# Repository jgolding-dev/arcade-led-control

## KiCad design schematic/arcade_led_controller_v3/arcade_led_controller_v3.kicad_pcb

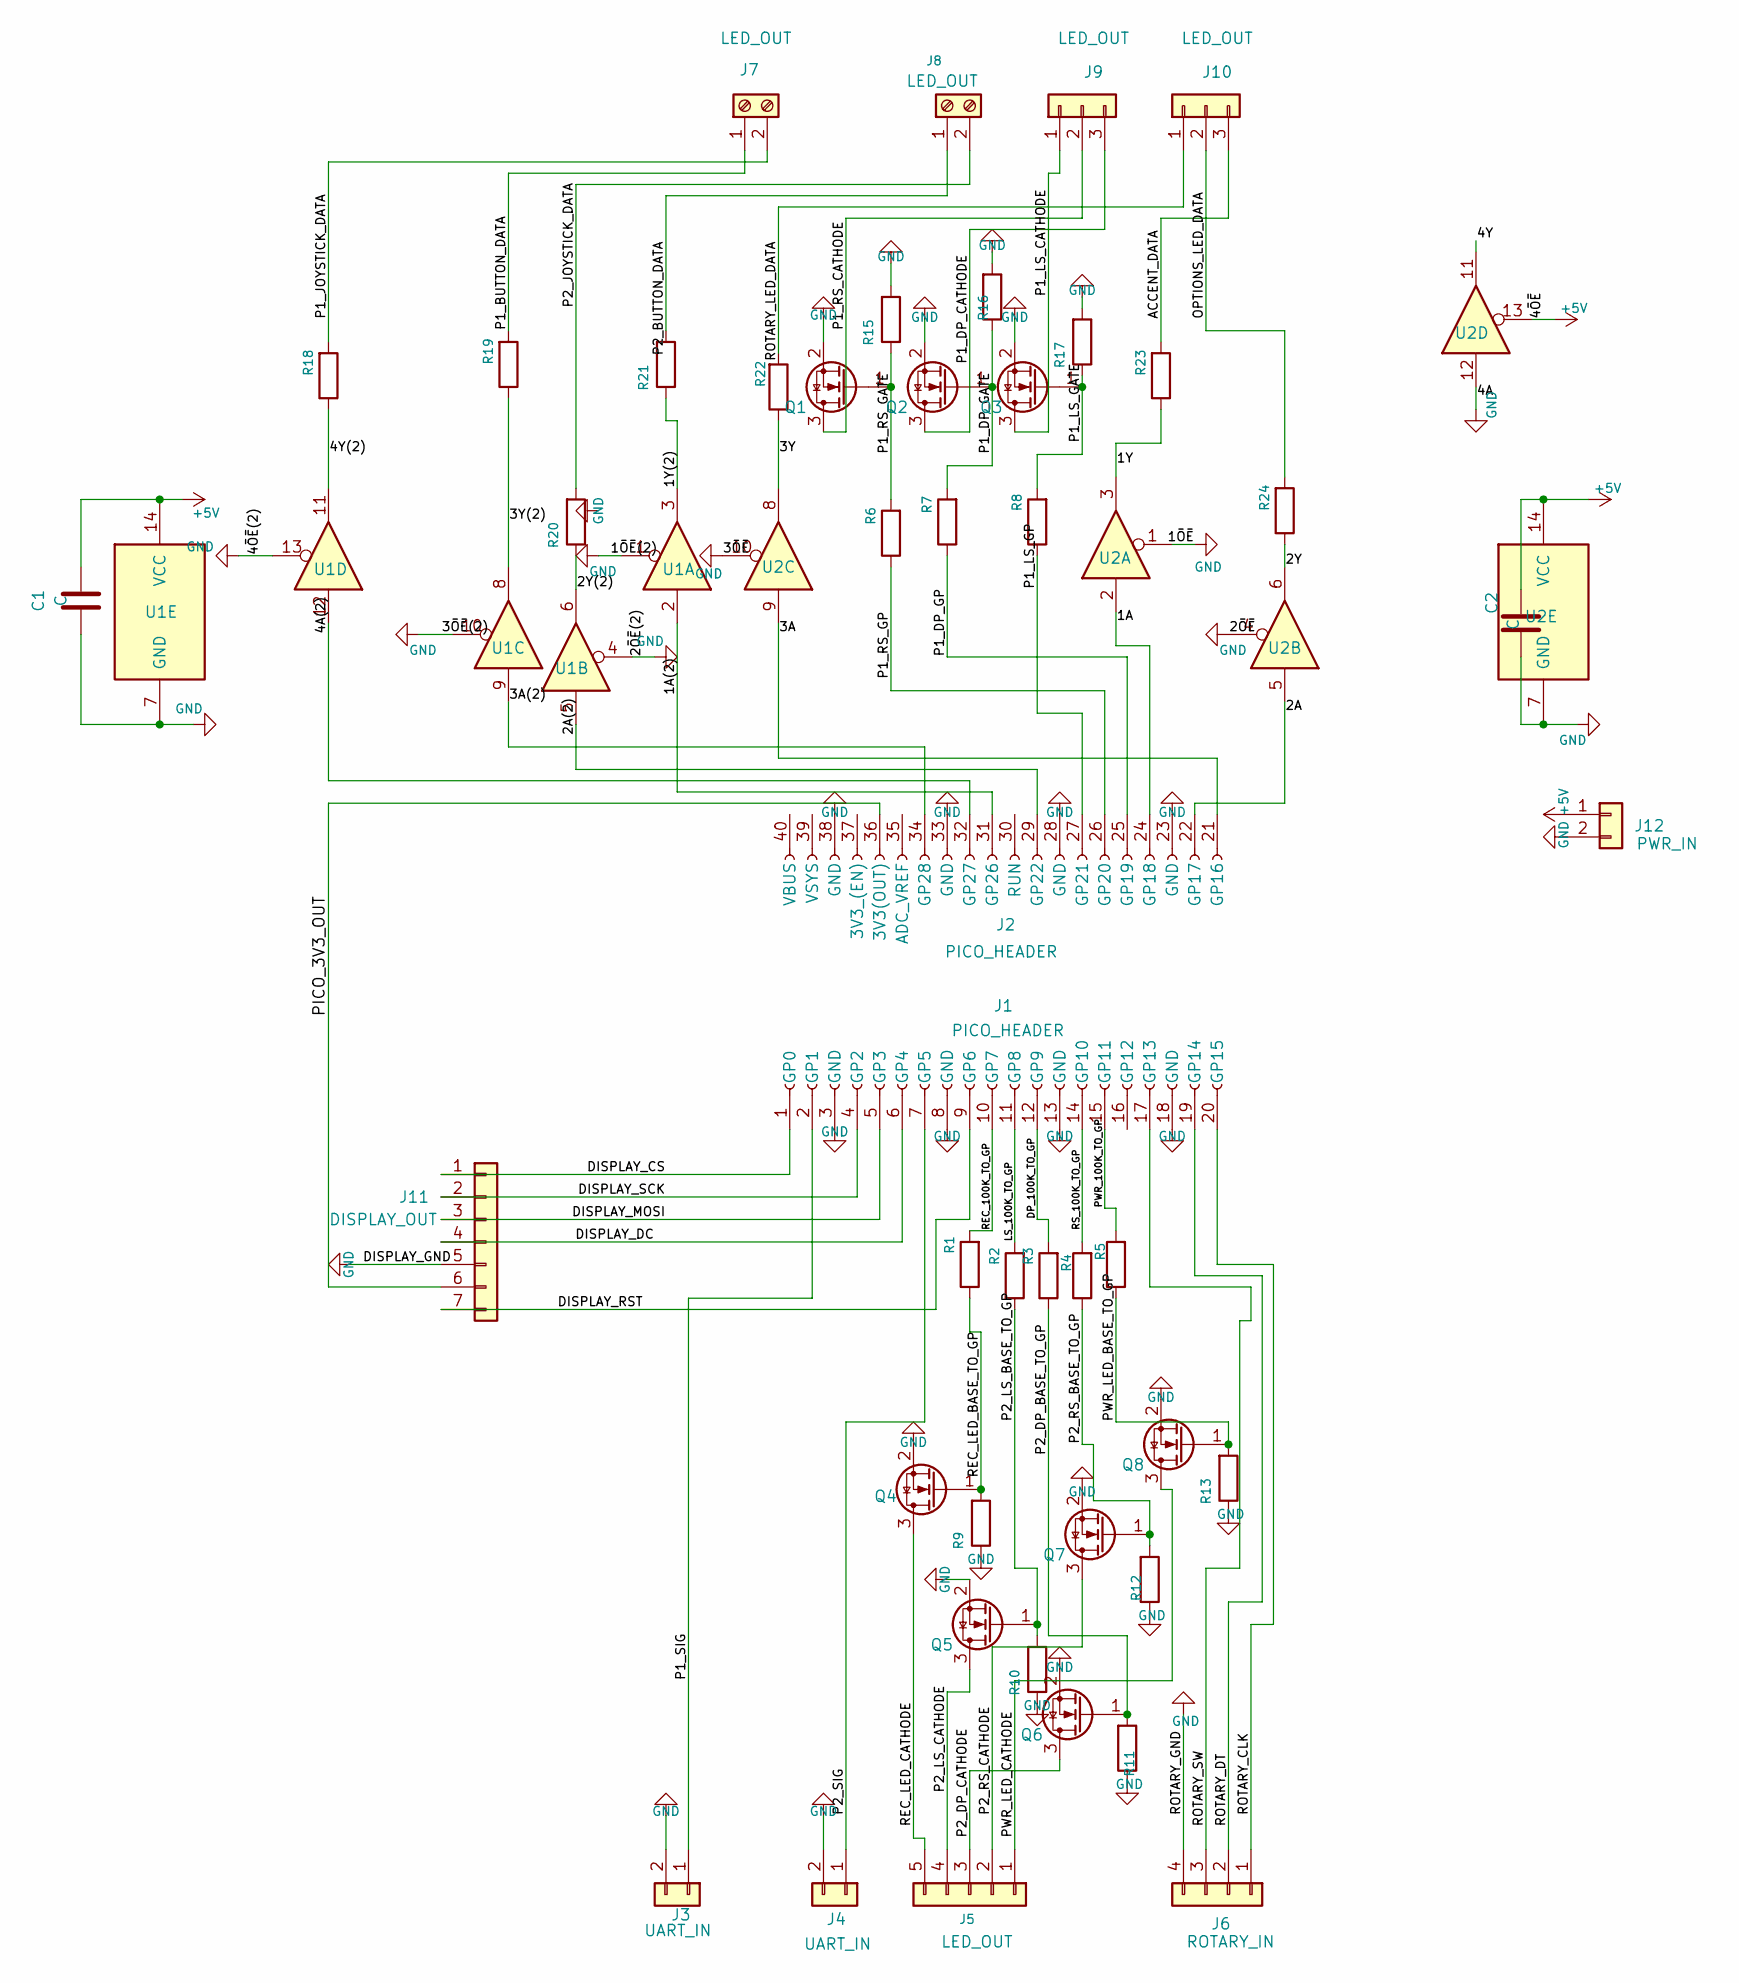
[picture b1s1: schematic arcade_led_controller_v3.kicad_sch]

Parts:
C1, C2: C; C_0805_2012Metric_Pad1.18x1.45mm_HandSolder
J1: PICO_HEADER; PinSocket_1x20_P2.54mm_Vertical_SMD_Pin1Left
J2: PICO_HEADER; PinSocket_1x20_P2.54mm_Vertical_SMD_Pin1Right
J3, J4: UART_IN; JST_PH_B2B-PH-SM4-TB_1x02-1MP_P2.00mm_Vertical
J5: LED_OUT; JST_PH_B5B-PH-SM4-TB_1x05-1MP_P2.00mm_Vertical
J6: ROTARY_IN; JST_PH_B4B-PH-SM4-TB_1x04-1MP_P2.00mm_Vertical
J7, J8: LED_OUT; JST_PH_B2B-PH-SM4-TB_1x02-1MP_P2.00mm_Vertical
J9, J10: LED_OUT; JST_PH_B3B-PH-SM4-TB_1x03-1MP_P2.00mm_Vertical
J11: DISPLAY_OUT; JST_PH_B7B-PH-SM4-TB_1x07-1MP_P2.00mm_Vertical
J12: PWR_IN; TerminalBlock_MetzConnect_Type086_RT03402HBLC_1x02_P3.81mm_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
Q1, Q2, Q3, Q4, Q5, Q6, Q7, Q8: Q_NMOS_GDS; SOT-23
R1, R2, R3, R4, R5, R6, R7, R8: 220Ω; R_0805_2012Metric_Pad1.20x1.40mm_HandSolder
R9, R10, R11, R12, R13, R15, R16, R17: 100kΩ; R_0805_2012Metric_Pad1.20x1.40mm_HandSolder
R18, R19, R20, R21, R22, R23, R24: 330Ω; R_0805_2012Metric_Pad1.20x1.40mm_HandSolder
U1, U2: 74AHCT125; SOIC-14_3.9x8.7mm_P1.27mm

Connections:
+5V: C1.2, C2.2, J12.1, U1.14 (VCC), U2.13, U2.14 (VCC); also elsewhere on the board
/1A: J2.24 (GP18), U2.2
/1A(2): J2.31 (GP26), U1.2
/1Y: R23.1, U2.3
/1Y(2): R21.1, U1.3
/2A: J2.22 (GP17), U2.5
/2A(2): J2.29 (GP22), U1.5
/2Y: R24.1, U2.6
/2Y(2): R20.1, U1.6
/3A: J2.21 (GP16), U2.9
/3A(2): J2.34 (GP28), U1.9
/3Y: R22.1, U2.8
/3Y(2): R19.1, U1.8
/4A(2): J2.32 (GP27), U1.12
/4Y: U2.11
/4Y(2): R18.1, U1.11
/ACCENT_DATA: J10.3, R23.2
/DISPLAY_CS: J1.1 (GP0), J11.1
/DISPLAY_DC: J1.6 (GP4), J11.4
/DISPLAY_MOSI: J1.5 (GP3), J11.3
/DISPLAY_RST: J1.9 (GP6), J11.7
/DISPLAY_SCK: J1.4 (GP2), J11.2
/DP_100K_TO_GP: J1.12 (GP9), R3.2
/LS_100K_TO_GP: J1.11 (GP8), R2.2
/OPTIONS_LED_DATA: J10.2, R24.2
/P1_BUTTON_DATA: J7.1, R19.2
/P1_DP_CATHODE: J9.3, Q2.3 (D)
/P1_DP_GATE: Q2.1 (G), R7.2, R16.1
/P1_DP_GP: J2.25 (GP19), R7.1
/P1_JOYSTICK_DATA: J7.2, R18.2
/P1_LS_CATHODE: J9.1, Q3.3 (D)
/P1_LS_GATE: Q3.1 (G), R8.2, R17.1
/P1_LS_GP: J2.27 (GP21), R8.1
/P1_RS_CATHODE: J9.2, Q1.3 (D)
/P1_RS_GATE: Q1.1 (G), R6.2, R15.1
/P1_RS_GP: J2.26 (GP20), R6.1
/P1_SIG: J1.2 (GP1), J3.1
/P2_BUTTON_DATA: J8.1, R21.2
/P2_DP_BASE_TO_GP: Q6.1 (G), R3.1, R11.2
/P2_DP_CATHODE: J5.3, Q6.3 (D)
/P2_JOYSTICK_DATA: J8.2, R20.2
/P2_LS_BASE_TO_GP: Q5.1 (G), R2.1, R10.2
/P2_LS_CATHODE: J5.4, Q5.3 (D)
/P2_RS_BASE_TO_GP: Q7.1 (G), R4.1, R12.2
/P2_RS_CATHODE: J5.2, Q7.3 (D)
/P2_SIG: J1.7 (GP5), J4.1
/PICO_3V3_OUT: J2.36 (3V3(OUT)), J11.6
/PWR_100K_TO_GP: J1.15 (GP11), R5.2
/PWR_LED_BASE_TO_GP: Q8.1 (G), R5.1, R13.2
/PWR_LED_CATHODE: J5.1, Q8.3 (D)
/REC_100K_TO_GP: J1.10 (GP7), R1.2
/REC_LED_BASE_TO_GP: Q4.1 (G), R1.1, R9.2
/REC_LED_CATHODE: J5.5, Q4.3 (D)
/ROTARY_CLK: J1.20 (GP15), J6.1
/ROTARY_DT: J1.19 (GP14), J6.2
/ROTARY_LED_DATA: J10.1, R22.2
/ROTARY_SW: J1.17 (GP13), J6.3
/RS_100K_TO_GP: J1.14 (GP10), R4.2
GND: C1.1, C2.1, J1.3 (GND), J1.8 (GND), J1.13 (GND), J1.18 (GND), J2.23 (GND), J2.28 (GND), J2.33 (GND), J2.38 (GND), J3.2, J4.2, J6.4, J11.5, J12.2, Q1.2 (S), Q2.2 (S), Q3.2 (S), Q4.2 (S), Q5.2 (S), Q6.2 (S), Q7.2 (S), Q8.2 (S), R9.1, R10.1, R11.1, R12.1, R13.1, R15.2, R16.2, R17.2, U1.1, U1.4, U1.7 (GND), U1.10, U1.13, U2.1, U2.4, U2.7 (GND), U2.10, U2.12; also elsewhere on the board

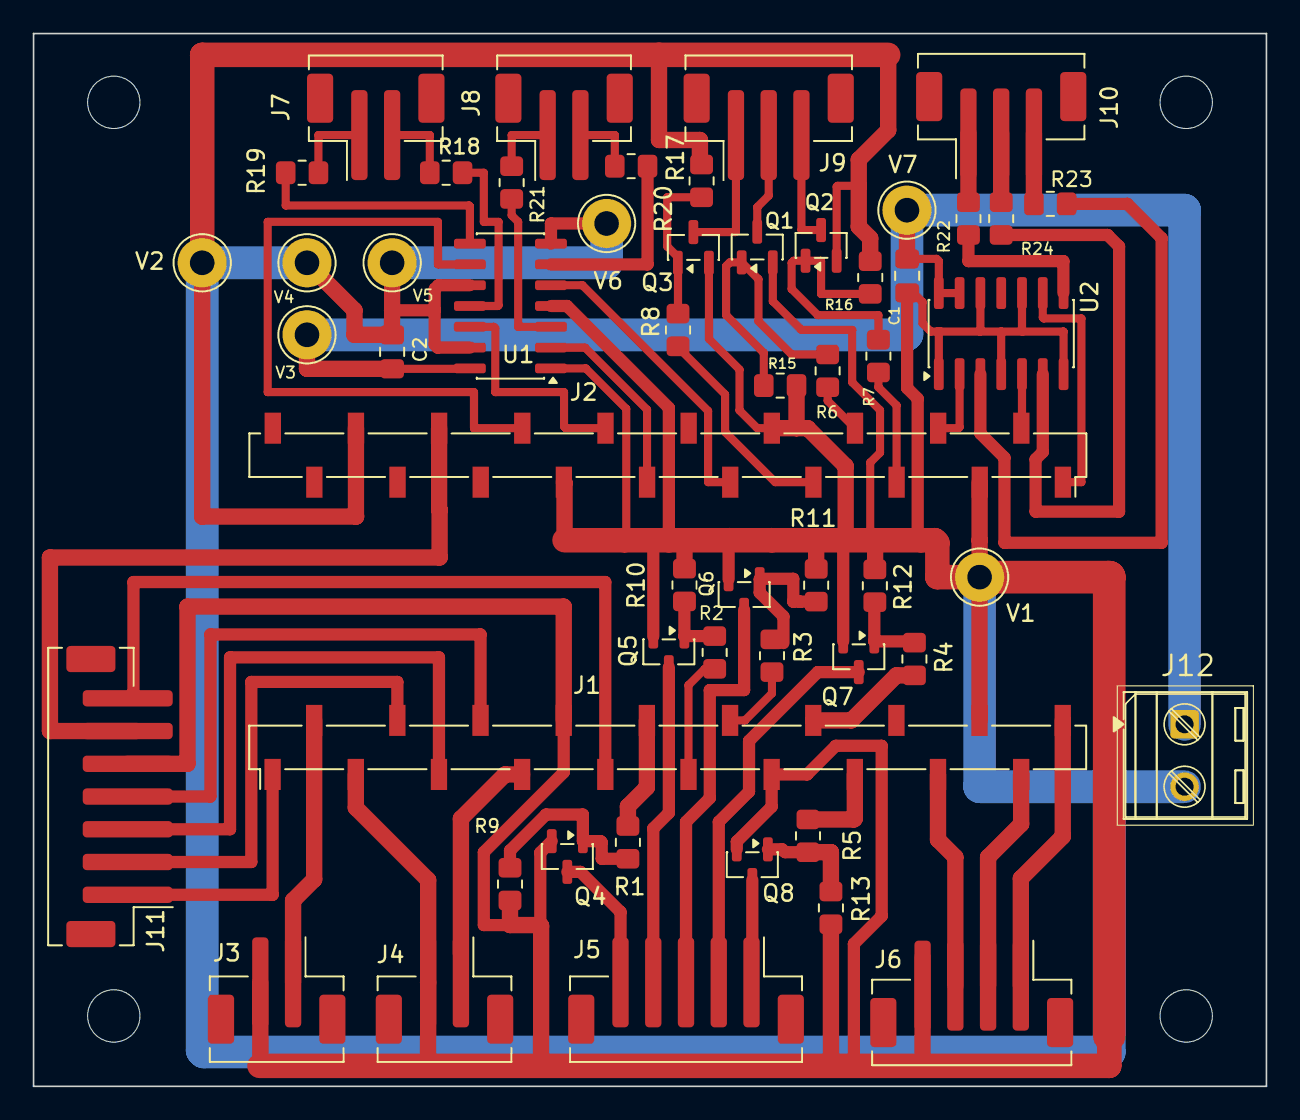
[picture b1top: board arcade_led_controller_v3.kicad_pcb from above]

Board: 2 copper layers, 75.3 x 64.3 mm, 54 parts (0 on the bottom side), 58 nets.

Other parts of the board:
V1, V2, V3, V4, V5, V6, V7: TestPoint_THTPad_D3.0mm_Drill1.5mm

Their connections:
+5V: V3.1, V7.1; also elsewhere on the board
GND: V1.1, V2.1, V4.1, V5.1, V6.1; also elsewhere on the board

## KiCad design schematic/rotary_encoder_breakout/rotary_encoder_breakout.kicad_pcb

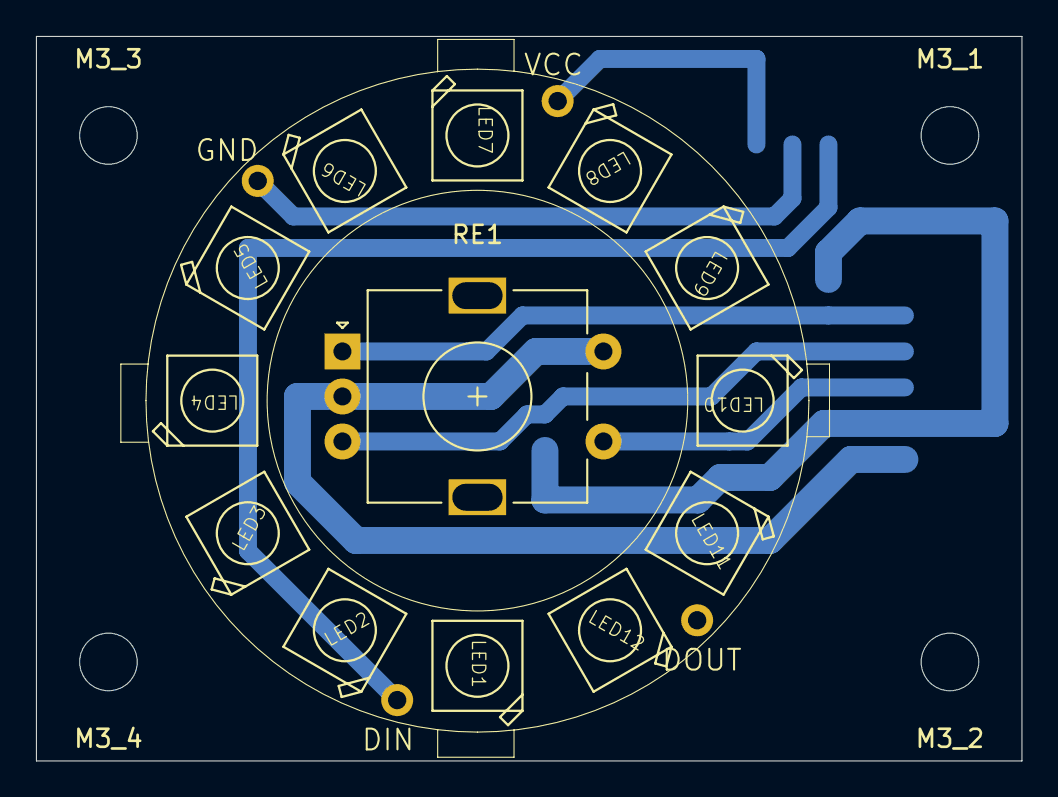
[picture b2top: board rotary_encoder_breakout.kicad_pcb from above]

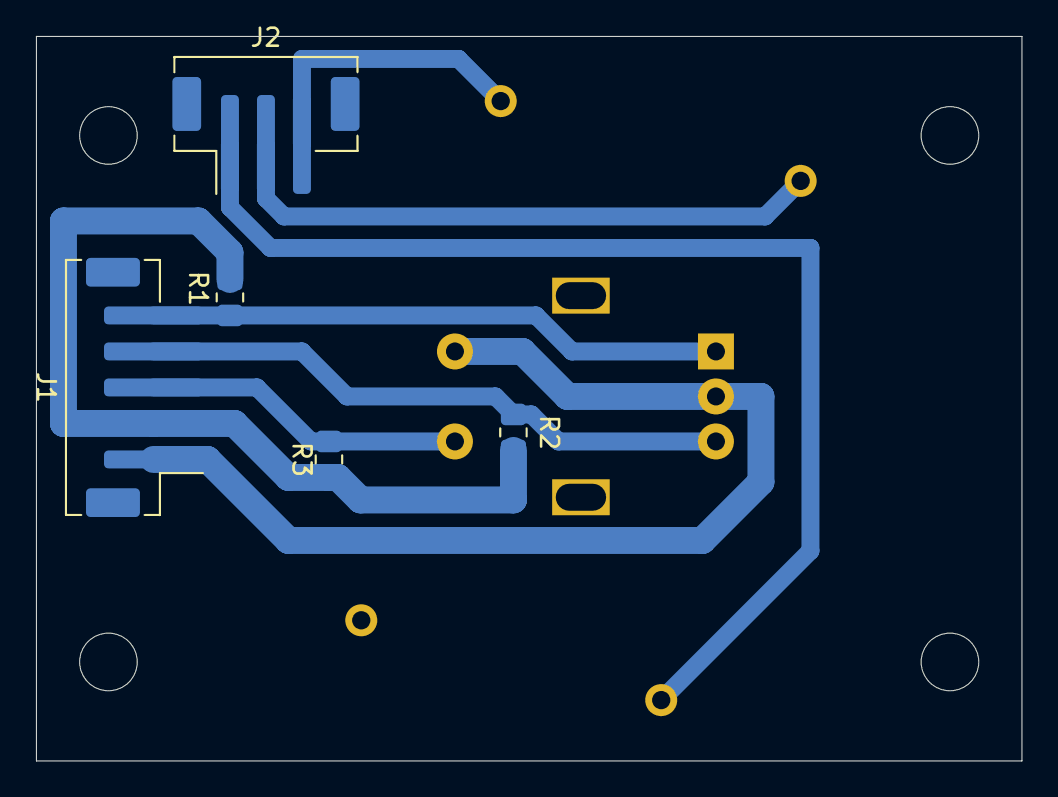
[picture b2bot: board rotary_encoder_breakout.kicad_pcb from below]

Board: 2 copper layers, 54.8 x 40.2 mm, 41 parts (10 on the bottom side), 7 nets.

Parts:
C2, C4, C6, C9, C10: 1uF; C0603_334
DIN: 1X01-CLEANBIG
DOUT: 1X01-CLEANBIG
GND: 1X01-CLEANBIG
J1: JST_Header_01x05; JST_PH_B5B-PH-SM4-TB_1x05-1MP_P2.00mm_Vertical
J2: Conn_01x04; JST_PH_B3B-PH-SM4-TB_1x03-1MP_P2.00mm_Vertical
LED1, LED2, LED3, LED4, LED5, LED6, LED7, LED8, LED9, LED10, LED11, LED12: WS2812B_5050N; WS2812B-NARROW
M3_1, M3_2, M3_3, M3_4: MountingHole_3.2mm_M3
PLABEL0: PLABEL0
PLABEL1: PLABEL1
PLABEL2: PLABEL2
PLABEL3: PLABEL3
PLABEL4: PLABEL4
PLABEL5: PLABEL5
PLABEL6: PLABEL6
PLABEL7: PLABEL7
PLABEL8: PLABEL8
R1: 470; 0603-NO
R1#2, R2, R3: 10k; R_0805_2012Metric_Pad1.20x1.40mm_HandSolder
RE1: RotaryEncoder_Switch; RotaryEncoder_Alps_EC11E-Switch_Vertical_H20mm
VCC: 1X01-CLEANBIG

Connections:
/CLK: J1.5, R1#2.2, RE1.A
/DT: J1.4, R2.1, RE1.B
/LED_DATA_IN: DIN.1, J2.1
/SW: J1.3, R3.2, RE1.S1
GND: GND.1, J1.1, J2.2, RE1.C, RE1.S2
VCC: J1.2, R1#2.1, R2.2, R3.1
VDD: J2.3, VCC.1

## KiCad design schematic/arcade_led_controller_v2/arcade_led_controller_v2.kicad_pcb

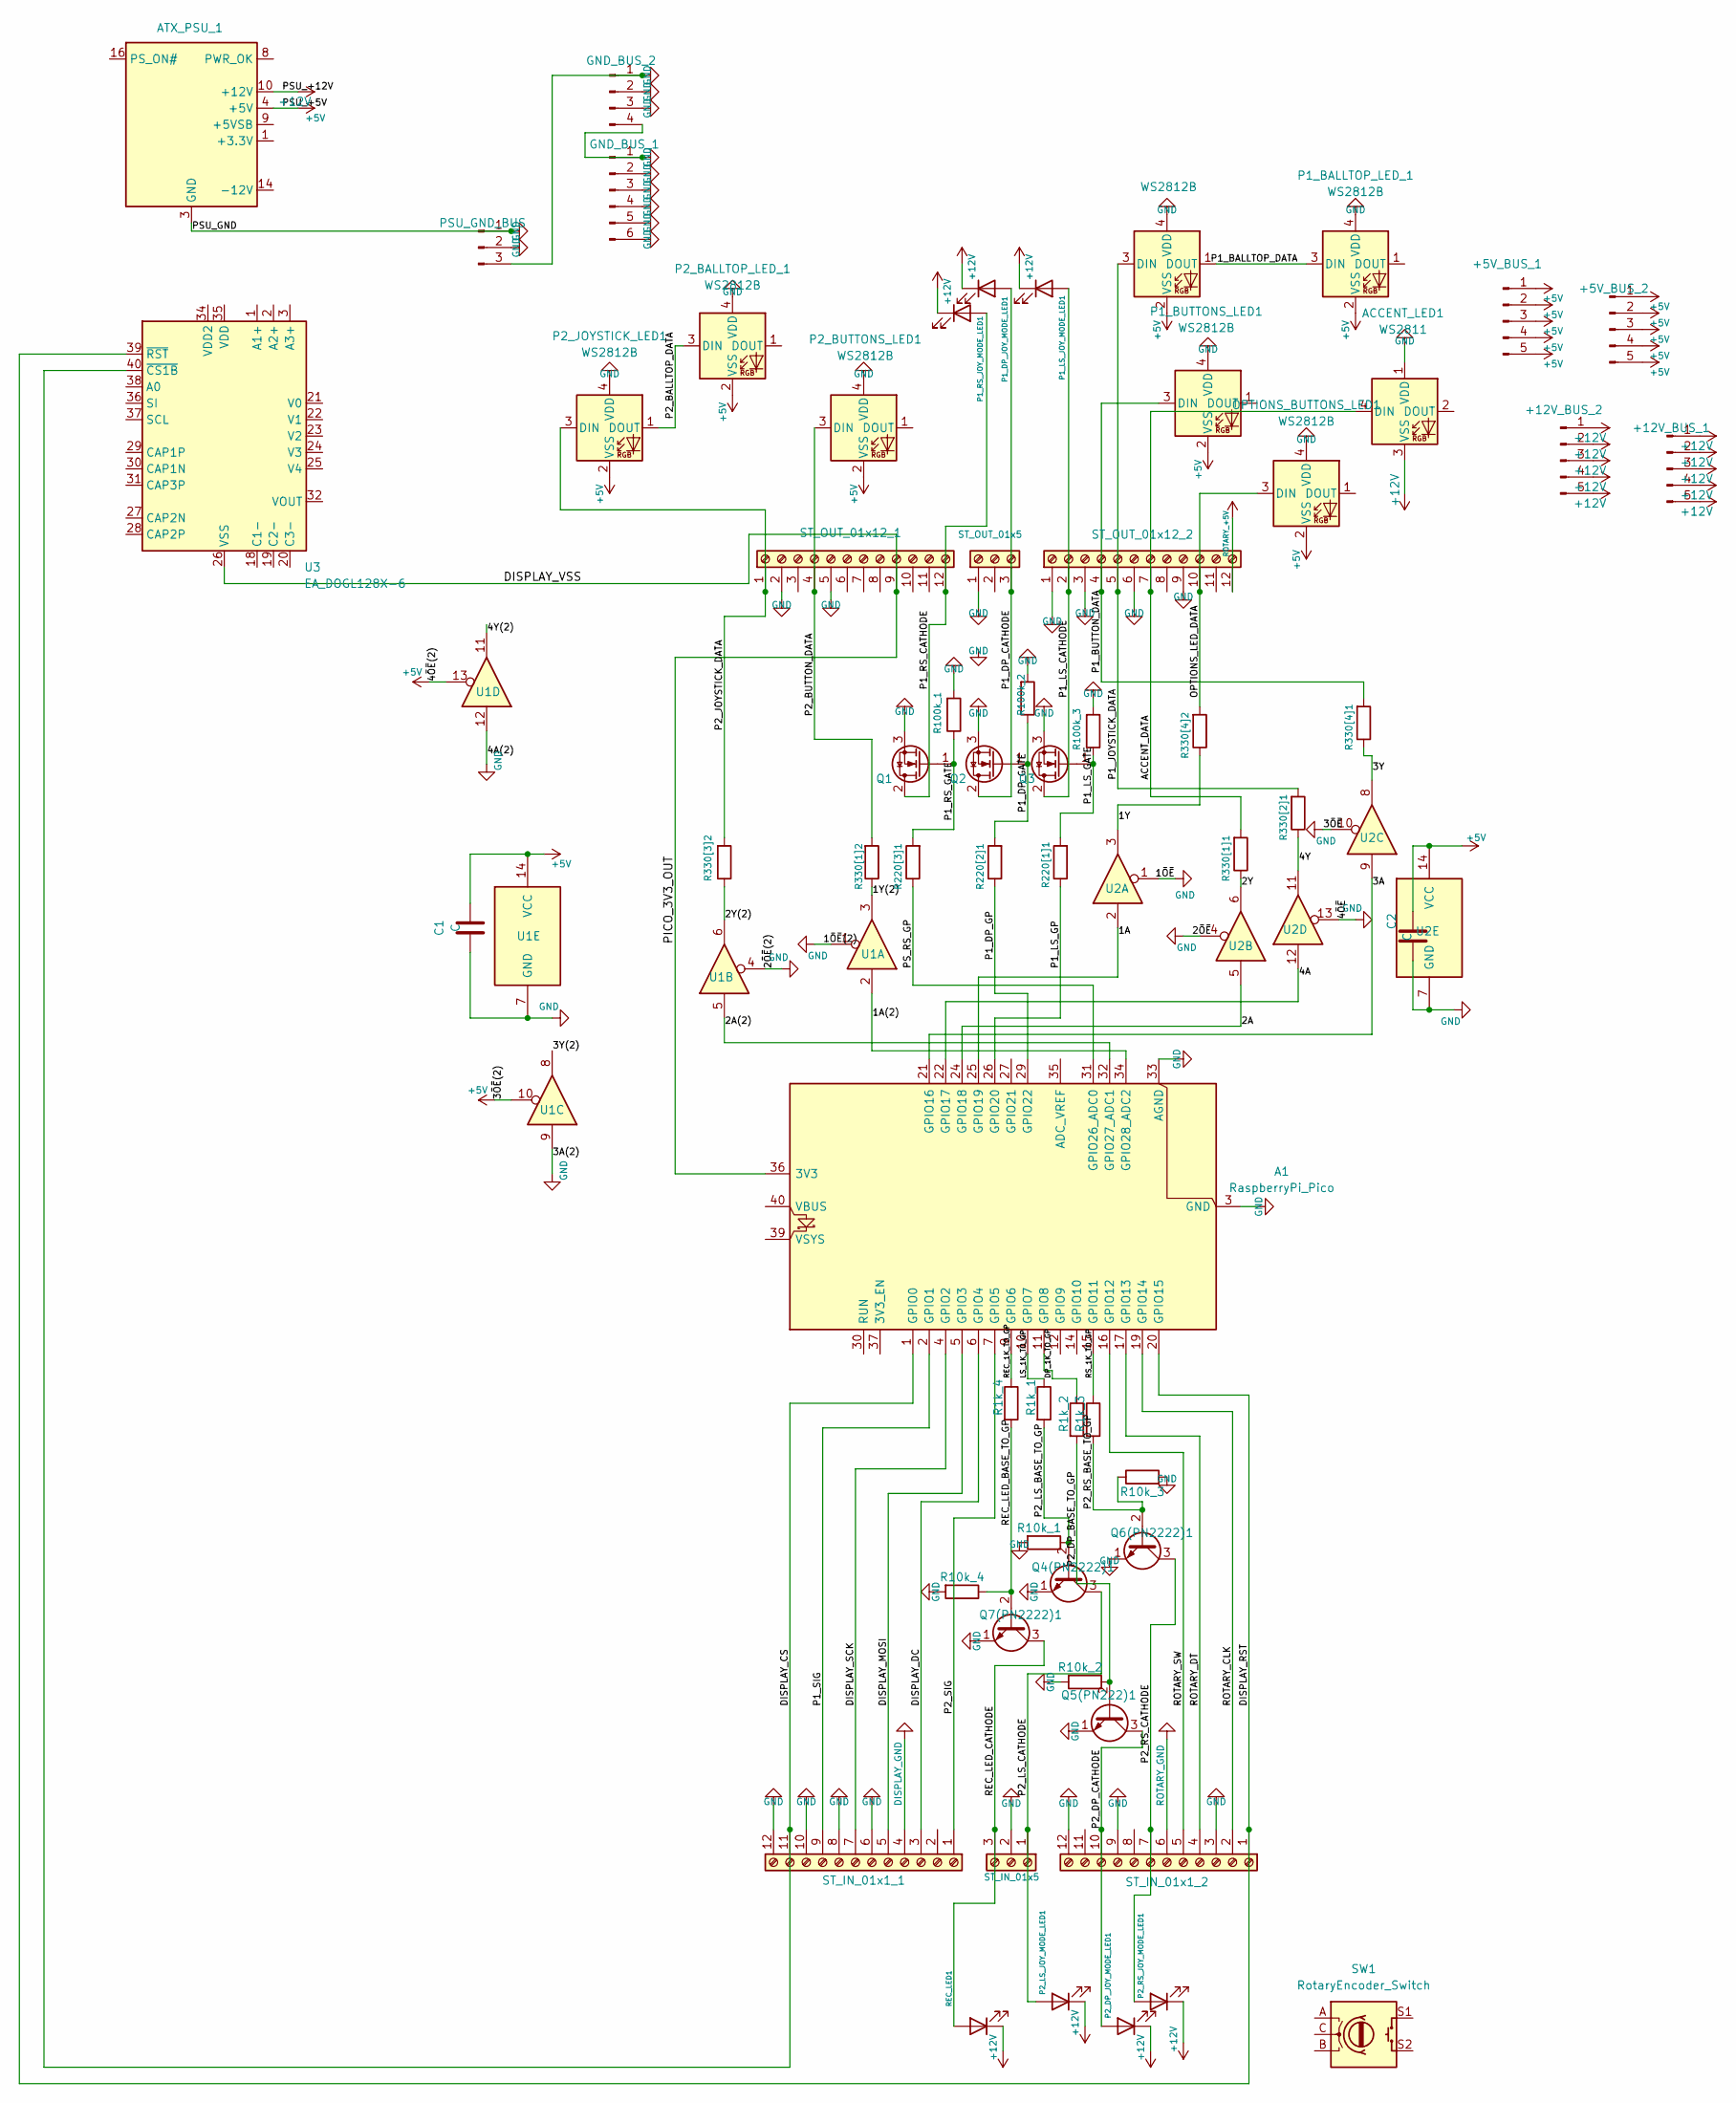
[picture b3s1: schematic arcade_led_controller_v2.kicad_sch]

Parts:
+5V_BUS_1, +5V_BUS_2: Conn_01x05_Pin; Wago_734-165_1x05_P3.50mm_Horizontal
+12V_BUS_1, +12V_BUS_2: Conn_01x05_Pin; TerminalBlock_WAGO_233-505_2x05_P2.54mm
A1: RaspberryPi_Pico; RaspberryPi_Pico_Common_THT
ACCENT_LED1: WS2811; LED_WS2812B_PLCC4_5.0x5.0mm_P3.2mm
ATX_PSU_1: ATX-24; Molex_Mini-Fit_Jr_5566-24A_2x12_P4.20mm_Vertical
C1, C2: C; C_Disc_D3.0mm_W1.6mm_P2.50mm
J1: GND_BUS_1; TerminalBlock_WAGO_233-506_2x06_P2.54mm
J2: GND_BUS_2; TerminalBlock_WAGO_233-504_2x04_P2.54mm
J3: PSU_GND_BUS; Wago_734-163_1x03_P3.50mm_Horizontal
OPTIONS_BUTTONS_LED1: WS2812B; LED_WS2812B-2020_PLCC4_2.0x2.0mm
P1_BALLTOP_LED_1, P1_BUTTONS_LED1, P1_JOYSTICK_LED1, P2_BALLTOP_LED_1, P2_BUTTONS_LED1, P2_JOYSTICK_LED1: WS2812B; LED_WS2812B-2020_PLCC4_2.0x2.0mm
P1_DP_JOY_MODE_LED1, P1_LS_JOY_MODE_LED1, P1_RS_JOY_MODE_LED1, P2_DP_JOY_MODE_LED1, P2_LS_JOY_MODE_LED1, P2_RS_JOY_MODE_LED1: LED; LED_D1.8mm_W1.8mm_H2.4mm_Horizontal_O3.81mm_Z1.6mm
Q1, Q2, Q3: Q_NMOS_GDS; TO-220-3_Vertical
Q4(PN2222)1, Q5(PN222)1, Q6(PN2222)1, Q7(PN2222)1: PN2222A; TO-92_Inline_Wide
R1k_1, R1k_2, R1k_3, R1k_4: 1kΩ; R_Axial_DIN0204_L3.6mm_D1.6mm_P5.08mm_Horizontal
R10k_1, R10k_2, R10k_3, R10k_4: 10kΩ; R_Axial_DIN0204_L3.6mm_D1.6mm_P5.08mm_Horizontal
R100k_1, R100k_2, R100k_3: 100kΩ; R_Axial_DIN0204_L3.6mm_D1.6mm_P5.08mm_Horizontal
R220[1]1, R220[2]1, R220[3]1: 220Ω; R_Axial_DIN0204_L3.6mm_D1.6mm_P5.08mm_Horizontal
R330[1]1, R330[1]2, R330[2]1, R330[3]2, R330[4]1, R330[4]2: 330Ω; R_Axial_DIN0204_L3.6mm_D1.6mm_P5.08mm_Horizontal
REC_LED1: LED; LED_D1.8mm_W1.8mm_H2.4mm_Horizontal_O3.81mm_Z1.6mm
ST_IN_01x1_1, ST_IN_01x1_2: Screw_Terminal_01x12; TerminalBlock_Phoenix_MPT-0,5-12-2.54_1x12_P2.54mm_Horizont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
ST_IN_01x5: Screw_Terminal_01x05; TerminalBlock_Phoenix_MPT-0,5-3-2.54_1x03_P2.54mm_Horizontal
ST_OUT_01x5: Screw_Terminal_01x05; TerminalBlock_Phoenix_MPT-0,5-3-2.54_1x03_P2.54mm_Horizontal
ST_OUT_01x12_1, ST_OUT_01x12_2: Screw_Terminal_01x12; TerminalBlock_Phoenix_MPT-0,5-12-2.54_1x12_P2.54mm_Horizont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
SW1: RotaryEncoder_Switch
U1, U2: 74AHCT125; DIP-14_W7.62mm
U3: EA_DOGL128X-6; EA_DOGL128-6

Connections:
+5V: +5V_BUS_1.1, +5V_BUS_1.2, +5V_BUS_1.3, +5V_BUS_1.4, +5V_BUS_1.5, +5V_BUS_2.1, +5V_BUS_2.2, +5V_BUS_2.3, +5V_BUS_2.4, +5V_BUS_2.5, ATX_PSU_1.4 (+5V), ATX_PSU_1.6 (+5V), ATX_PSU_1.21 (+5V), ATX_PSU_1.22 (+5V), ATX_PSU_1.23 (+5V), C1.2, C2.2, OPTIONS_BUTTONS_LED1.2 (VSS), P1_BALLTOP_LED_1.2 (VSS), P1_BUTTONS_LED1.2 (VSS), P1_JOYSTICK_LED1.2 (VSS), P2_BALLTOP_LED_1.2 (VSS), P2_BUTTONS_LED1.2 (VSS), P2_JOYSTICK_LED1.2 (VSS), U1.10, U1.13, U1.14 (VCC), U2.14 (VCC)
+12V: +12V_BUS_1.1, +12V_BUS_1.2, +12V_BUS_1.3, +12V_BUS_1.4, +12V_BUS_1.5, +12V_BUS_2.1, +12V_BUS_2.2, +12V_BUS_2.3, +12V_BUS_2.4, +12V_BUS_2.5, ACCENT_LED1.3 (VSS), ATX_PSU_1.10 (+12V), ATX_PSU_1.11 (+12V), P1_DP_JOY_MODE_LED1.1 (K), P1_LS_JOY_MODE_LED1.1 (K), P1_RS_JOY_MODE_LED1.1 (K), P2_DP_JOY_MODE_LED1.1 (K), P2_LS_JOY_MODE_LED1.1 (K), P2_RS_JOY_MODE_LED1.1 (K), REC_LED1.1 (K)
/1A: A1.25 (GPIO19), U2.2
/1A(2): A1.34 (GPIO28_ADC2), U1.2
/1Y: R330[4]2.1, U2.3
/1Y(2): R330[1]2.1, U1.3
/2A: A1.24 (GPIO18), U2.5
/2A(2): A1.32 (GPIO27_ADC1), U1.5
/2Y: R330[1]1.1, U2.6
/2Y(2): R330[3]2.1, U1.6
/3A: A1.21 (GPIO16), U2.9
/3Y: R330[4]1.1, U2.8
/3Y(2): U1.8
/4A: A1.22 (GPIO17), U2.12
/4Y: R330[2]1.1, U2.11
/4Y(2): U1.11
/ACCENT_DATA: ACCENT_LED1.4 (DIN), R330[1]1.2, ST_OUT_01x12_2.7
/DISPLAY_CS: A1.1 (GPIO0), ST_IN_01x1_1.11, U3.40 (~CS1B)
/DISPLAY_DC: A1.6 (GPIO4), ST_IN_01x1_1.3
/DISPLAY_MOSI: A1.5 (GPIO3), ST_IN_01x1_1.5
/DISPLAY_RST: A1.20 (GPIO15), ST_IN_01x1_2.1, U3.39 (~RST)
/DISPLAY_SCK: A1.4 (GPIO2), ST_IN_01x1_1.7
/DISPLAY_VSS: A1.36 (3V3), ST_OUT_01x12_1.9, U3.26 (VSS), U3.33 (VSS)
/DP_1K_TO_GP: A1.11 (GPIO8), R1k_2.1
/LS_1K_TO_GP: A1.10 (GPIO7), R1k_1.1
/OPTIONS_LED_DATA: OPTIONS_BUTTONS_LED1.3 (DIN), R330[4]2.2, ST_OUT_01x12_2.10
/P1_BALLTOP_DATA: P1_BALLTOP_LED_1.3 (DIN), P1_JOYSTICK_LED1.1 (DOUT)
/P1_BUTTON_DATA: P1_BUTTONS_LED1.3 (DIN), R330[4]1.2, ST_OUT_01x12_2.4
/P1_DP_CATHODE: P1_DP_JOY_MODE_LED1.2 (A), Q2.2 (D), ST_OUT_01x5.3
/P1_DP_GATE: Q2.1 (G), R100k_2.1, R220[2]1.2
/P1_DP_GP: A1.29 (GPIO22), R220[2]1.1
/P1_JOYSTICK_DATA: P1_JOYSTICK_LED1.3 (DIN), R330[2]1.2, ST_OUT_01x12_2.5
/P1_LS_CATHODE: P1_LS_JOY_MODE_LED1.2 (A), Q3.2 (D), ST_OUT_01x12_2.2
/P1_LS_GATE: Q3.1 (G), R100k_3.1, R220[1]1.2
/P1_LS_GP: A1.26 (GPIO20), R220[1]1.1
/P1_RS_CATHODE: P1_RS_JOY_MODE_LED1.2 (A), Q1.2 (D), ST_OUT_01x12_1.12
/P1_RS_GATE: Q1.1 (G), R100k_1.1, R220[3]1.2
/P1_SIG: A1.2 (GPIO1), ST_IN_01x1_1.9
/P2_BALLTOP_DATA: P2_BALLTOP_LED_1.3 (DIN), P2_JOYSTICK_LED1.1 (DOUT)
/P2_BUTTON_DATA: P2_BUTTONS_LED1.3 (DIN), R330[1]2.2, ST_OUT_01x12_1.4
/P2_DP_BASE_TO_GP: Q5(PN222)1.2 (B), R1k_2.2, R10k_2.1
/P2_DP_CATHODE: P2_DP_JOY_MODE_LED1.2 (A), Q5(PN222)1.3 (C), ST_IN_01x1_2.10
/P2_JOYSTICK_DATA: P2_JOYSTICK_LED1.3 (DIN), R330[3]2.2, ST_OUT_01x12_1.1
/P2_LS_BASE_TO_GP: Q4(PN2222)1.2 (B), R1k_1.2, R10k_1.1
/P2_LS_CATHODE: P2_LS_JOY_MODE_LED1.2 (A), Q4(PN2222)1.3 (C), ST_IN_01x5.1
/P2_RS_BASE_TO_GP: Q6(PN2222)1.2 (B), R1k_3.2, R10k_3.1
/P2_RS_CATHODE: P2_RS_JOY_MODE_LED1.2 (A), Q6(PN2222)1.3 (C), ST_IN_01x1_2.7
/P2_SIG: A1.7 (GPIO5), ST_IN_01x1_1.1
/PS_RS_GP: A1.31 (GPIO26_ADC0), R220[3]1.1
/REC_1K_TO_GP: A1.9 (GPIO6), R1k_4.1
/REC_LED_BASE_TO_GP: Q7(PN2222)1.2 (B), R1k_4.2, R10k_4.1
/REC_LED_CATHODE: Q7(PN2222)1.3 (C), REC_LED1.2 (A), ST_IN_01x5.3
/ROTARY_CLK: A1.19 (GPIO14), ST_IN_01x1_2.2
/ROTARY_DT: A1.17 (GPIO13), ST_IN_01x1_2.4
/ROTARY_SW: A1.16 (GPIO12), ST_IN_01x1_2.5
/RS_1K_TO_GP: A1.15 (GPIO11), R1k_3.1
DISPLAY_GND: ST_IN_01x1_1.4
GND: A1.3 (GND), A1.8 (GND), A1.13 (GND), A1.18 (GND), A1.23 (GND), A1.28 (GND), A1.33 (AGND), A1.38 (GND), ACCENT_LED1.1 (VDD), ATX_PSU_1.3 (GND), ATX_PSU_1.5 (GND), ATX_PSU_1.7 (GND), ATX_PSU_1.15 (GND), ATX_PSU_1.17 (GND), ATX_PSU_1.18 (GND), ATX_PSU_1.19 (GND), ATX_PSU_1.24 (GND), C1.1, C2.1, J1.1, J1.2, J1.3, J1.4, J1.5, J1.6, J2.1, J2.2, J2.3, J2.4, J3.1, J3.2, J3.3, OPTIONS_BUTTONS_LED1.4 (VDD), P1_BALLTOP_LED_1.4 (VDD), P1_BUTTONS_LED1.4 (VDD), P1_JOYSTICK_LED1.4 (VDD), P2_BALLTOP_LED_1.4 (VDD), P2_BUTTONS_LED1.4 (VDD), P2_JOYSTICK_LED1.4 (VDD), Q1.3 (S), Q2.3 (S), Q3.3 (S), Q4(PN2222)1.1 (E), Q5(PN222)1.1 (E), Q6(PN2222)1.1 (E), Q7(PN2222)1.1 (E), R10k_1.2, R10k_2.2, R10k_3.2, R10k_4.2, R100k_1.2, R100k_2.2, R100k_3.2, ST_IN_01x1_1.6, ST_IN_01x1_1.8, ST_IN_01x1_1.10, ST_IN_01x1_1.12, ST_IN_01x1_2.3, ST_IN_01x1_2.9, ST_IN_01x1_2.12, ST_IN_01x5.2, ST_OUT_01x5.1, ST_OUT_01x12_1.2, ST_OUT_01x12_1.5, ST_OUT_01x12_2.1, ST_OUT_01x12_2.3, ST_OUT_01x12_2.6, ST_OUT_01x12_2.9, U1.1, U1.4, U1.7 (GND), U1.9, U1.12, U2.1, U2.4, U2.7 (GND), U2.10, U2.13
unnamed: ATX_PSU_1.1 (+3.3V), ATX_PSU_1.2 (+3.3V), ATX_PSU_1.12 (+3.3V), ATX_PSU_1.13 (+3.3V)
ROTARY_+5V: ST_OUT_01x12_2.12
ROTARY_GND: ST_IN_01x1_2.6

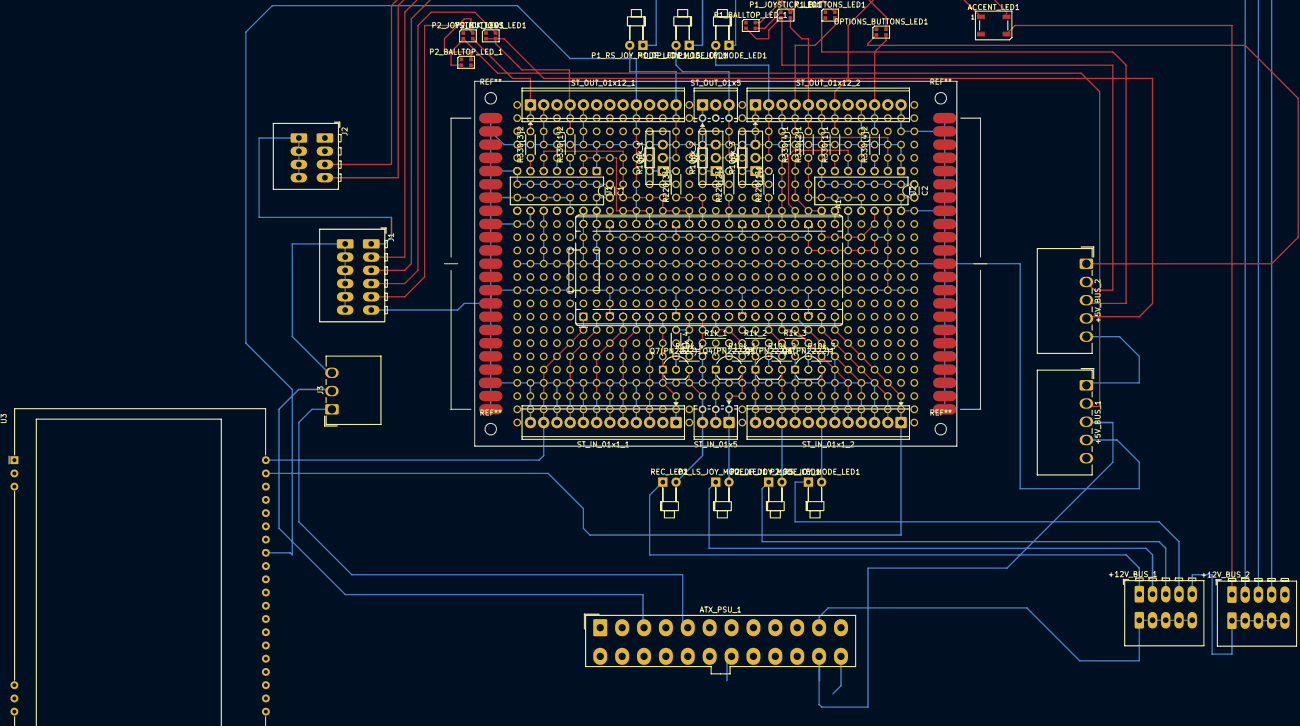
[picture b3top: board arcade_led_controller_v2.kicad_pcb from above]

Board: 2 copper layers, 92.5 x 70.0 mm, 62 parts (0 on the bottom side), 56 nets.

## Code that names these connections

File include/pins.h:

#ifndef pins_h
#define pins_h

#include <Arduino.h>

// ---------------- Output ---------------- //

#define ACCENT_DATA_PIN                   18
#define OPTIONS_BUTTONS_DATA_PIN          19

#define PLAYER1_BUTTONS_DATA_PIN          16
#define PLAYER1_JOY_DATA_PIN         17

#define P1_LS_MODE_PIN                    20
#define P1_DP_MODE_PIN                    22
#define P1_RS_MODE_PIN                    26

#define PLAYER2_BUTTONS_DATA_PIN          28
#define PLAYER2_JOY_DATA_PIN         27     

#define REC_BUTTON_LED_PIN                6
#define P2_LS_MODE_PIN                    7
#define P2_DP_MODE_PIN                    8
#define P2_RS_MODE_PIN                    11

// ---------------- Input ---------------- //

#define P2_UART_RX_PIN                    5
#define DISPLAY_SCK_PIN                   2
#define DISPLAY_MOSI_PIN                  3
#define DISPLAY_CS_PIN                    0
#define DISPLAY_DC_PIN                    4

#define ROTARY_SW_PIN                     12
#define ROTARY_DT_PIN                     13
#define ROTARY_CLK_PIN                    14
#define DISPLAY_RST_PIN                   15

#define P1_UART_RX_PIN                    1

// ---------------- Groups ---------------- //

class Pins {
public:
  static void initPins() {
    // Options
    pinMode(OPTIONS_BUTTONS_DATA_PIN, OUTPUT);
    pinMode(REC_BUTTON_LED_PIN, OUTPUT);

    // Player 1
    pinMode(PLAYER1_BUTTONS_DATA_PIN, OUTPUT);
    pinMode(PLAYER1_JOY_DATA_PIN, OUTPUT);

    // Player 2
    pinMode(PLAYER2_BUTTONS_DATA_PIN, OUTPUT);
    pinMode(PLAYER2_JOY_DATA_PIN, OUTPUT);

    // Joystick Modes
    pinMode(P1_LS_MODE_PIN, OUTPUT);
    pinMode(P1_DP_MODE_PIN, OUTPUT);
    pinMode(P1_RS_MODE_PIN, OUTPUT);
    pinMode(P2_LS_MODE_PIN, OUTPUT);
    pinMode(P2_DP_MODE_PIN, OUTPUT);
    pinMode(P2_RS_MODE_PIN, OUTPUT);

    // Accent Lighting
    pinMode(ACCENT_DATA_PIN, OUTPUT);

    // Display Output
    pinMode(DISPLAY_SCK_PIN, OUTPUT);
    pinMode(DISPLAY_MOSI_PIN, OUTPUT);
    pinMode(DISPLAY_CS_PIN, OUTPUT);
    pinMode(DISPLAY_DC_PIN, OUTPUT);
    pinMode(DISPLAY_RST_PIN, OUTPUT);

    // Rotary Input
    pinMode(ROTARY_SW_PIN, INPUT_PULLUP);
    pinMode(ROTARY_DT_PIN, INPUT_PULLUP);
    pinMode(ROTARY_CLK_PIN, INPUT_PULLUP);
  }
};

#endif

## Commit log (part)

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2025-12-23 establish-project
2025-12-25 fix compilation errors
2025-12-26 Implement Static Color effect
2025-12-26 Initial zone file structure
2025-12-27 common package
2025-12-27 Initial Zone hierarchy setup
2025-12-28 zone initial implementation
2026-01-01 animations
2026-01-01 Refactor animation controller
2026-01-02 Build out zone classes
2026-01-02 Consolidate zone headers into one file
2026-01-03 Restructure project files, and fix compilation errors
2026-01-03 fix FastLED configuration
2026-01-03 Make LED_ZONES list polymorphic for proper child class overrides
2026-01-08 zone and animation updates & fixes
2026-01-08 migrate project to PlatformIO
2026-01-12 refactoring...
2026-01-17 implement full zone
2026-04-12 bug fixes
2026-04-12 switch to earlephilhower pico core
2026-04-12 implement custom lighting presets
2026-04-12 Update pin mappings
2026-04-12 make options W2812B type LEDs
2026-04-12 optimize functions (pass-by-reference/pointer)
2026-04-12 add kicad schematic
2026-04-17 initial UART RX
2026-04-18 upgrade to full packet-parser
2026-04-19 harden packet parser
2026-04-20 define input enums, and upgrade validation to crc8
2026-04-20 upgrade parser to non-blocking state machine
2026-04-20 fix bug in parser
2026-04-25 parser length bug fix, and additional logging
2026-04-25 uart input to LED mapping
2026-04-26 clean up debug logs
2026-04-26 expand uart parsing to player 2, and incorporate idle timeout handling
2026-04-26 setup structure for button input to LED lookup tables
2026-04-29 Fix usb instability issues
2026-05-02 Add controller disconnect handling
2026-05-03 schematic updates
2026-05-04 Update input pin assignments
2026-05-04 update net classes
2026-05-04 complete track routing
2026-05-05 wrapping up v2 schematic and pcb changes. Update pins.h to match
2026-05-11 logging updates
2026-05-18 setup crgb color pallete and blend animation data
2026-05-25 update default gp2040 config image
2026-05-25 swap p1 and p2 uart pins
2026-05-27 ditch custom color struct in favor of CRGB
2026-05-29 handle record button LED, and replace brightness hard-coding with constants
2026-05-29 Revert P1 and P2 UART Pin swap to fix usb enumeration failure caused by uart pin initialization order
2026-05-29 Bring back custom RGB_t data structure
2026-06-01 fix sf_turbo preset color mappings
2026-06-03 Implement zone switch animation
2026-06-04 initial animation class structure
2026-06-06 fix full zone messing up modifier index of sub zones
2026-06-06 update button to LED mappings
2026-06-07 update button to LED mapping arrays
2026-06-07 implement blend animation
2026-06-09 fix broken sf-turbo lighting pattern
2026-06-09 separate balltop LED array, and implement color shift animation
2026-06-09 Add modifier control for color shift animation speed
2026-06-09 fix player 2 sf-turbo lighting pattern
2026-06-10 correct for GRB/RGB mismatch by creating logical buffer array, and translating to output array before showing LED states
2026-06-10 initial input-to-LED-index processing structure
2026-06-13 implement rotary volume control
2026-06-17 fix Full zone animations not showing updates
2026-06-19 defining input-to-LED-index mapping structures
2026-06-19 initial button input processing framework
2026-06-25 initialize and manage input processors
2026-06-27 integrate input processor with animation controller
2026-06-29 Cap maximum brightness to limit unnecessary power draw
2026-06-30 do not animate full zone when its not active
2026-06-30 Change brightness cap
